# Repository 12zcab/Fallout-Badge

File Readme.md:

# Soupa Cool Badge for FallOut:D

Erm yah why not build a Badge with Z80 instead of ESP32 :)

Slack Username:12zcab

# What it can do?

1.Display ur Detail on 1602 LCD

2.use joystick and 6 Buttons to control the device

3.Plug it onto ur computer and have more interaction through console!

AND THE MOST IMPORTANT POINT IS: ITS HACKABLE!!!!!!!!!

U can easily reprogram it by overriding data on the EEPROM

# Main Components
Pls refer to BOM.csv for more details
1.Z80 10MHz
2.Z80 PIO 10MHz IC
3.MS6850 Serial IC
4.WC1602A LCD Display
5.Push Buttons
6.5 Direction Mini Joystick
7.on Board CH340

# Images

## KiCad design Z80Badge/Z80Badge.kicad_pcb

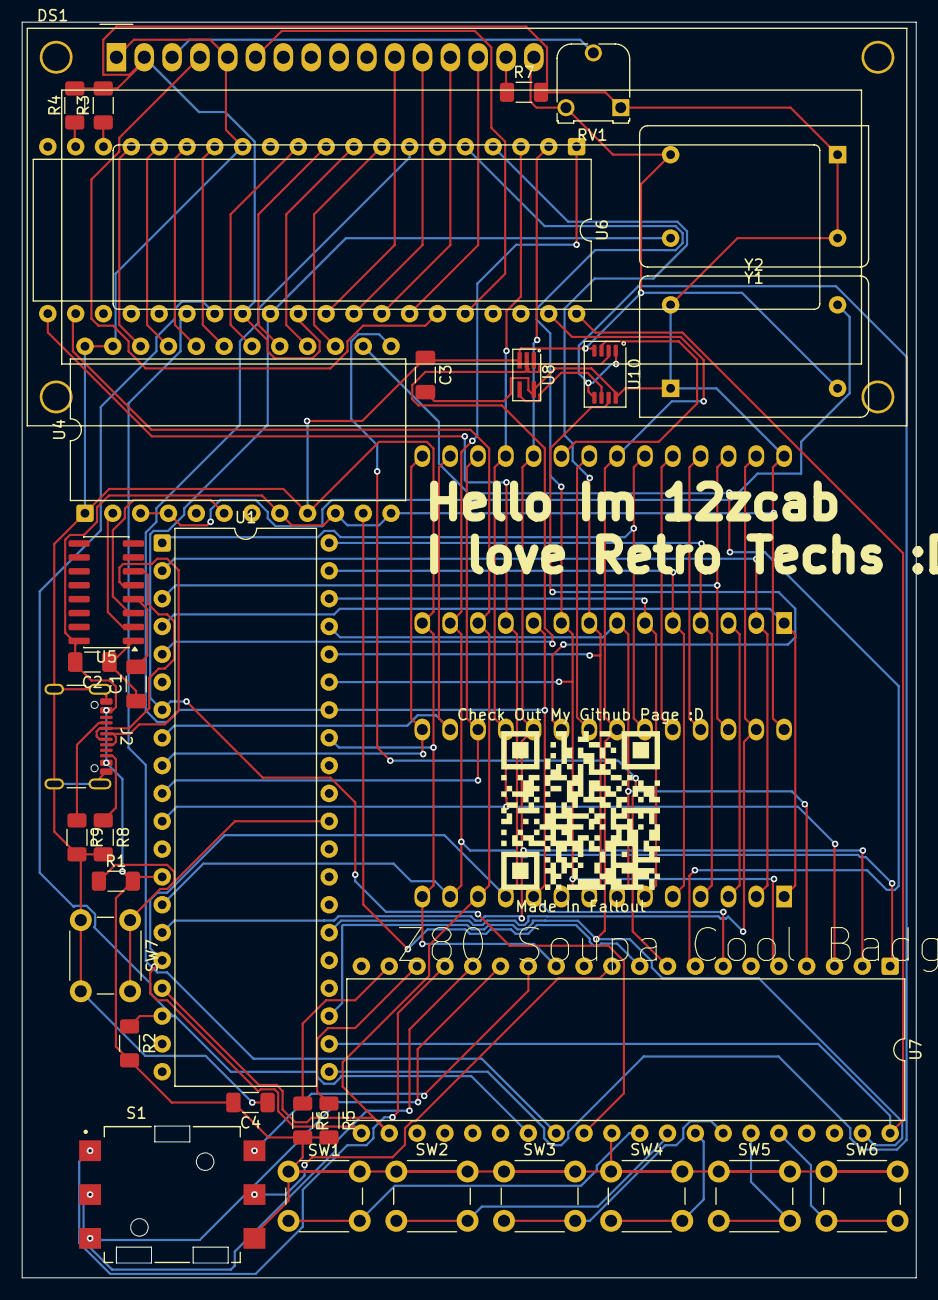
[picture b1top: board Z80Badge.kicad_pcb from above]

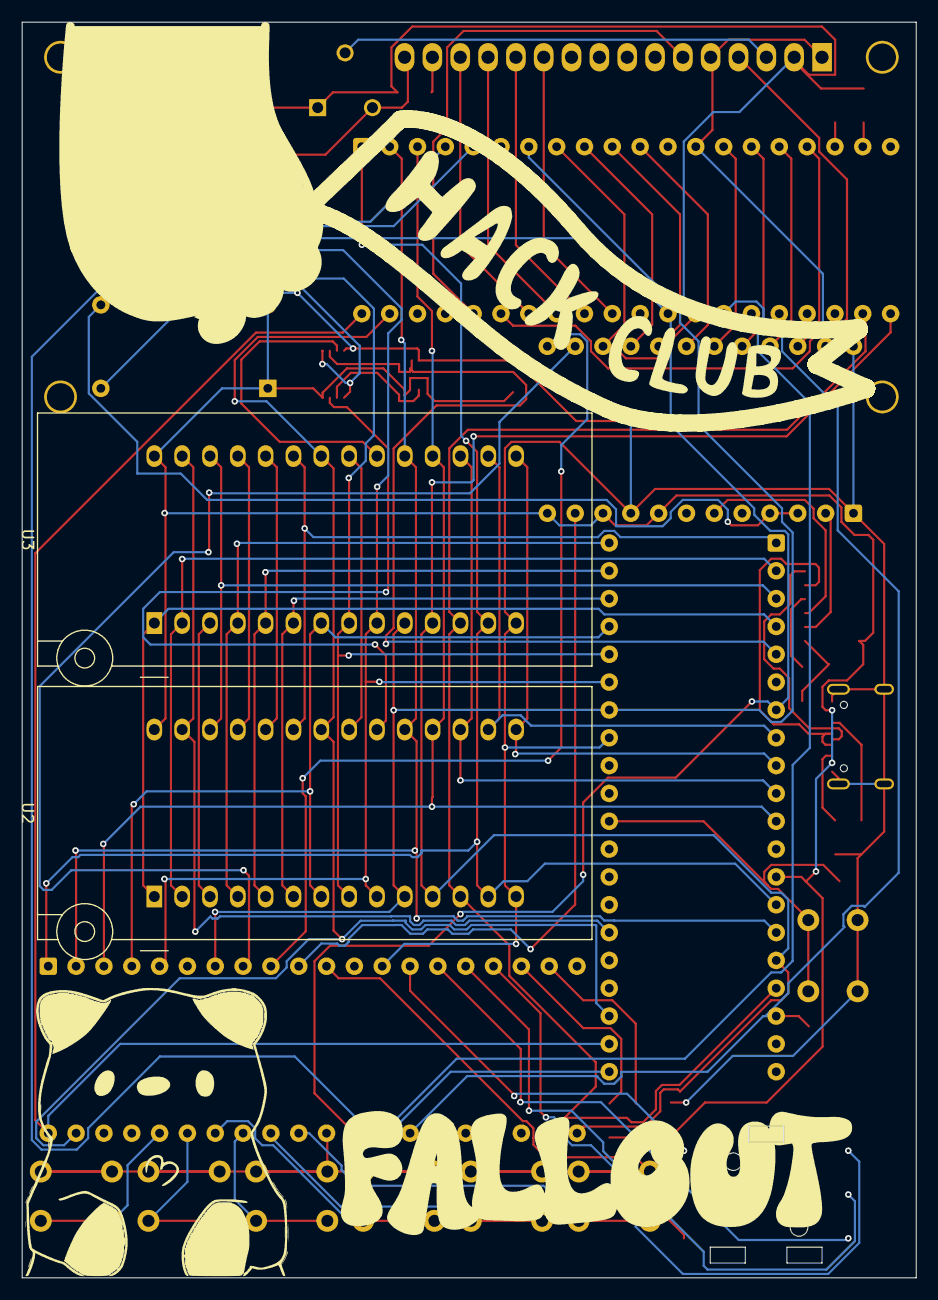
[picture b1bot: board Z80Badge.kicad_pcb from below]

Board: 2 copper layers, 81.6 x 114.6 mm, 36 parts (2 on the bottom side), 80 nets.

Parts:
C1: 0.1uF; C_1206_3216Metric_Pad1.33x1.80mm_HandSolder
C2: CH340C 100nF; C_1206_3216Metric_Pad1.33x1.80mm_HandSolder
C3: 6850 100nF; C_1206_3216Metric_Pad1.33x1.80mm_HandSolder
C4: Z80 100nF; C_1206_3216Metric_Pad1.33x1.80mm_HandSolder
DS1: WC1602A
J2: USB_C_Receptacle_USB2.0_16P; USB_C_Receptacle_GCT_USB4105-xx-A_16P_TopMnt_Horizontal
Made In Fallout: Check Out My Github Page :D; //github.com/12zcab?tab=repositories
R1, R2, R3, R4, R5, R6: 10k_PLUP; R_1206_3216Metric_Pad1.30x1.75mm_HandSolder
R7: 330; R_1206_3216Metric_Pad1.30x1.75mm_HandSolder
R8, R9: 5.1k_PLDN; R_1206_3216Metric_Pad1.30x1.75mm_HandSolder
RV1: R_Potentiometer_10K_RM065; Potentiometer_Runtron_RM-065_Vertical
S1: JS5208; SW_JS5208
SW1, SW2, SW3, SW4, SW5, SW6, SW7: SW_Push; SW_PUSH_6mm
U1: Z84C00_DIP_10MHz; DIP-40_W15.24mm
U2: 28C256; DIP_Socket-28_W11.9mm_W12.7mm_W15.24mm_W17.78mm_W18.5mm_3M_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
U3: CY62256-70PC; DIP_Socket-28_W11.9mm_W12.7mm_W15.24mm_W17.78mm_W18.5mm_3M_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
U4: MC6850; DIP-24_W15.24mm
U5: CH340C; SOIC-16_3.9x9.9mm_P1.27mm
U6, U7: Z84C20_DIP; DIP-40_W15.24mm
U8: 74AHC1G04; SOT-353_SC-70-5_Handsoldering
U10: 74LVC2G32; TSSOP-8_3x3mm_P0.65mm
Y1: 10MHz; Oscillator_DIP-14
Y2: 2.4576; Oscillator_DIP-14

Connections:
/1602_D4: DS1.11 (D4), U6.31 (PB_{0})
/1602_D5: DS1.12 (D5), U6.32 (PB_{1})
/1602_D6: DS1.13 (D6), U6.33 (PB_{2})
/1602_D7: DS1.14 (D7), U6.34 (PB_{3})
/1602_E: DS1.6 (E), U6.36 (PB_{5})
/1602_RS: DS1.4 (RS), U6.35 (PB_{4})
/6850_D0: U4.22 (D0), U6.17 (PA_{0})
/6850_D1: U4.21 (D1), U6.16 (PA_{1})
/6850_D2: U4.20 (D2), U6.15 (PA_{2})
/6850_D3: U4.19 (D3), U6.14 (PA_{3})
/6850_D4: U4.18 (D4), U6.11 (PA_{4})
/6850_D5: U4.17 (D5), U6.10 (PA_{5})
/6850_D6: U4.16 (D6), U6.9 (PA_{6})
/6850_D7: U4.15 (D7), U6.8 (PA_{7})
/6850_E: U4.14 (E), U7.8 (PA_{7})
/6850_RS: U4.11 (RS), U7.10 (PA_{5})
/6850_RW: U4.13 (R/~W), U7.9 (PA_{6})
/A0: U1.34 (A_{0}), U2.10 (A0), U3.10 (A0), U6.7 (B/~A), U7.7 (B/~A)
/A1: U1.35 (A_{1}), U2.9 (A1), U3.9 (A1), U6.5 (C/~D), U7.5 (C/~D)
/A2: U1.36 (A_{2}), U2.8 (A2), U3.8 (A2), U6.4 (~CE)
/A3: U1.37 (A_{3}), U2.7 (A3), U3.7 (A3), U7.4 (~CE)
/A4: U1.38 (A_{4}), U2.6 (A4), U3.6 (A4)
/A5: U1.39 (A_{5}), U2.5 (A5), U3.5 (A5)
/A6: U1.40 (A_{6}), U2.4 (A6), U3.4 (A6)
/A7: U2.3 (A7), U3.3 (A7)
/A8: U2.25 (A8), U3.25 (A8)
/A9: U2.24 (A9), U3.24 (A9)
/A10: U2.21 (A10), U3.21 (A10)
/A11: U1.1 (A_{11}), U2.23 (A11), U3.23 (A11)
/A12: U1.2 (A_{12}), U2.2 (A12), U3.2 (A12)
/A13: U1.3 (A_{13}), U2.26 (A13), U3.26 (A13)
/A14: U1.4 (A_{14}), U2.1 (A14), U3.1 (A14)
/A15: U1.5 (A_{15}), U8.2, U10.2
/CH340C_Rx: U4.6 (Tx_Data), U5.3 (RXD)
/CH340C_Tx: U4.2 (Rx_Data), U5.2 (TXD)
/D0: U1.16 (D_{0}), U2.11 (D0), U3.11 (Q0), U6.21 (D_{0}), U7.21 (D_{0})
/D1: U1.17 (D_{1}), U2.12 (D1), U3.12 (Q1), U6.22 (D_{1}), U7.22 (D_{1})
/D2: U1.14 (D_{2}), U2.13 (D2), U3.13 (Q2), U6.1 (D_{2}), U7.1 (D_{2})
/D3: U1.9 (D_{3}), U2.15 (D3), U3.15 (Q3)
/D4: U1.8 (D_{4}), U2.16 (D4), U3.16 (Q4)
/D5: U1.10 (D_{5}), U2.17 (D5), U3.17 (Q5)
/D6: U1.11 (D_{6}), U2.18 (D6), U3.18 (Q6), U6.3 (D_{6}), U7.3 (D_{6})
/D7: U1.15 (D_{7}), U2.19 (D7), U3.19 (Q7), U6.2 (D_{7}), U7.2 (D_{7})
/EEPROM_CS: U2.20 (~CS), U10.7
/GND: C3.1, C4.1, DS1.1 (VSS), DS1.5 (R/W), DS1.16 (LED(-)), J2.A1 (GND), J2.A12 (GND), J2.B1 (GND), J2.B12 (GND), J2.SH (SHIELD), R8.2, R9.2, RV1.3, SW7.2, U1.33 (GND), U2.14 (GND), U3.14 (GND), U4.1 (VSS), U4.9 (CS2), U4.23 (~DCD), U4.24 (~CTS), U6.13 (GND), U7.13 (GND), U8.3 (GND), U10.4 (GND), Y1.7 (GND), Y2.7 (GND)
/J1: S1.1, U7.17 (PA_{0})
/J2: S1.2, U7.16 (PA_{1})
/J3: S1.3, U7.15 (PA_{2})
/J4: S1.4, U7.14 (PA_{3})
/J5: S1.5, U7.11 (PA_{4})
/PIO1IE0: U6.26 (IEO), U7.28 (IEI)
/SRAM_CS: U3.20 (~CS), U10.3
/SW1: SW1.2, U7.31 (PB_{0})
/SW2: SW2.2, U7.32 (PB_{1})
/SW3: SW4.2, U7.33 (PB_{2})
/SW4: SW3.2, U7.34 (PB_{3})
/SW5: SW5.2, U7.35 (PB_{4})
/SW6: SW6.2, U7.36 (PB_{5})
/VCC: C2.2, C3.2, C4.2, DS1.2 (VDD), J2.A4 (VBUS), J2.A9 (VBUS), J2.B4 (VBUS), J2.B9 (VBUS), R1.2, R2.2, R3.2, R4.2, R5.2, R6.2, R7.2, RV1.1, S1.6, SW1.1, SW2.1, SW3.1, SW4.1, SW5.1, SW6.1, U1.13 (V_{CC}), U2.28 (VCC), U3.28 (VCC), U4.8 (CS0), U4.10 (CS1), U4.12 (VCC), U5.16 (VCC), U6.28 (IEI), U6.30 (V_{CC}), U7.30 (V_{CC}), U8.5 (VCC), U10.8 (VCC), Y1.1 (EN), Y1.14 (Vcc), Y2.1 (EN), Y2.14 (Vcc)
/~CLK: U1.7 (~CLK), U6.29 (CLK), U7.29 (CLK), Y1.8 (OUT)
/~INT: R2.1, U1.18 (~INT), U6.27 (~INT), U7.27 (~INT)
/~IORQ: U1.22 (~IORQ), U6.40 (~IORQ), U7.40 (~IORQ)
/~MREQ: U1.21 (~MREQ), U10.1, U10.5
/~RD: U1.23 (~RD), U2.22 (~OE), U3.22 (~OE), U6.39 (~RD), U7.39 (~RD)
/~RESET: R1.1, SW7.1, U1.30 (~RESET)
/~WR: U1.26 (~WR), U2.27 (~WE), U3.27 (~WE)
unnamed: DS1.15 (LED(+)), R7.1
unnamed: DS1.3 (VO), RV1.2
unnamed: J2.A5 (CC1), R9.1
unnamed: J2.B5 (CC2), R8.1
unnamed: U4.3 (Rx_CLK), U4.4 (Tx_CLK), Y2.8 (OUT)
unnamed: C1.1, C2.1, U5.1 (GND)
unnamed: J2.A6 (D+), J2.B6 (D+), U5.5 (UD+)
unnamed: J2.A7 (D-), J2.B7 (D-), U5.6 (UD-)
unnamed: C1.2, U5.4 (V3)
unnamed: R3.1, U6.18 (~ASTB)
unnamed: R4.1, U6.19 (~BSTB)
unnamed: R5.1, U7.18 (~ASTB)
unnamed: R6.1, U7.19 (~BSTB)
unnamed: U8.4, U10.6
